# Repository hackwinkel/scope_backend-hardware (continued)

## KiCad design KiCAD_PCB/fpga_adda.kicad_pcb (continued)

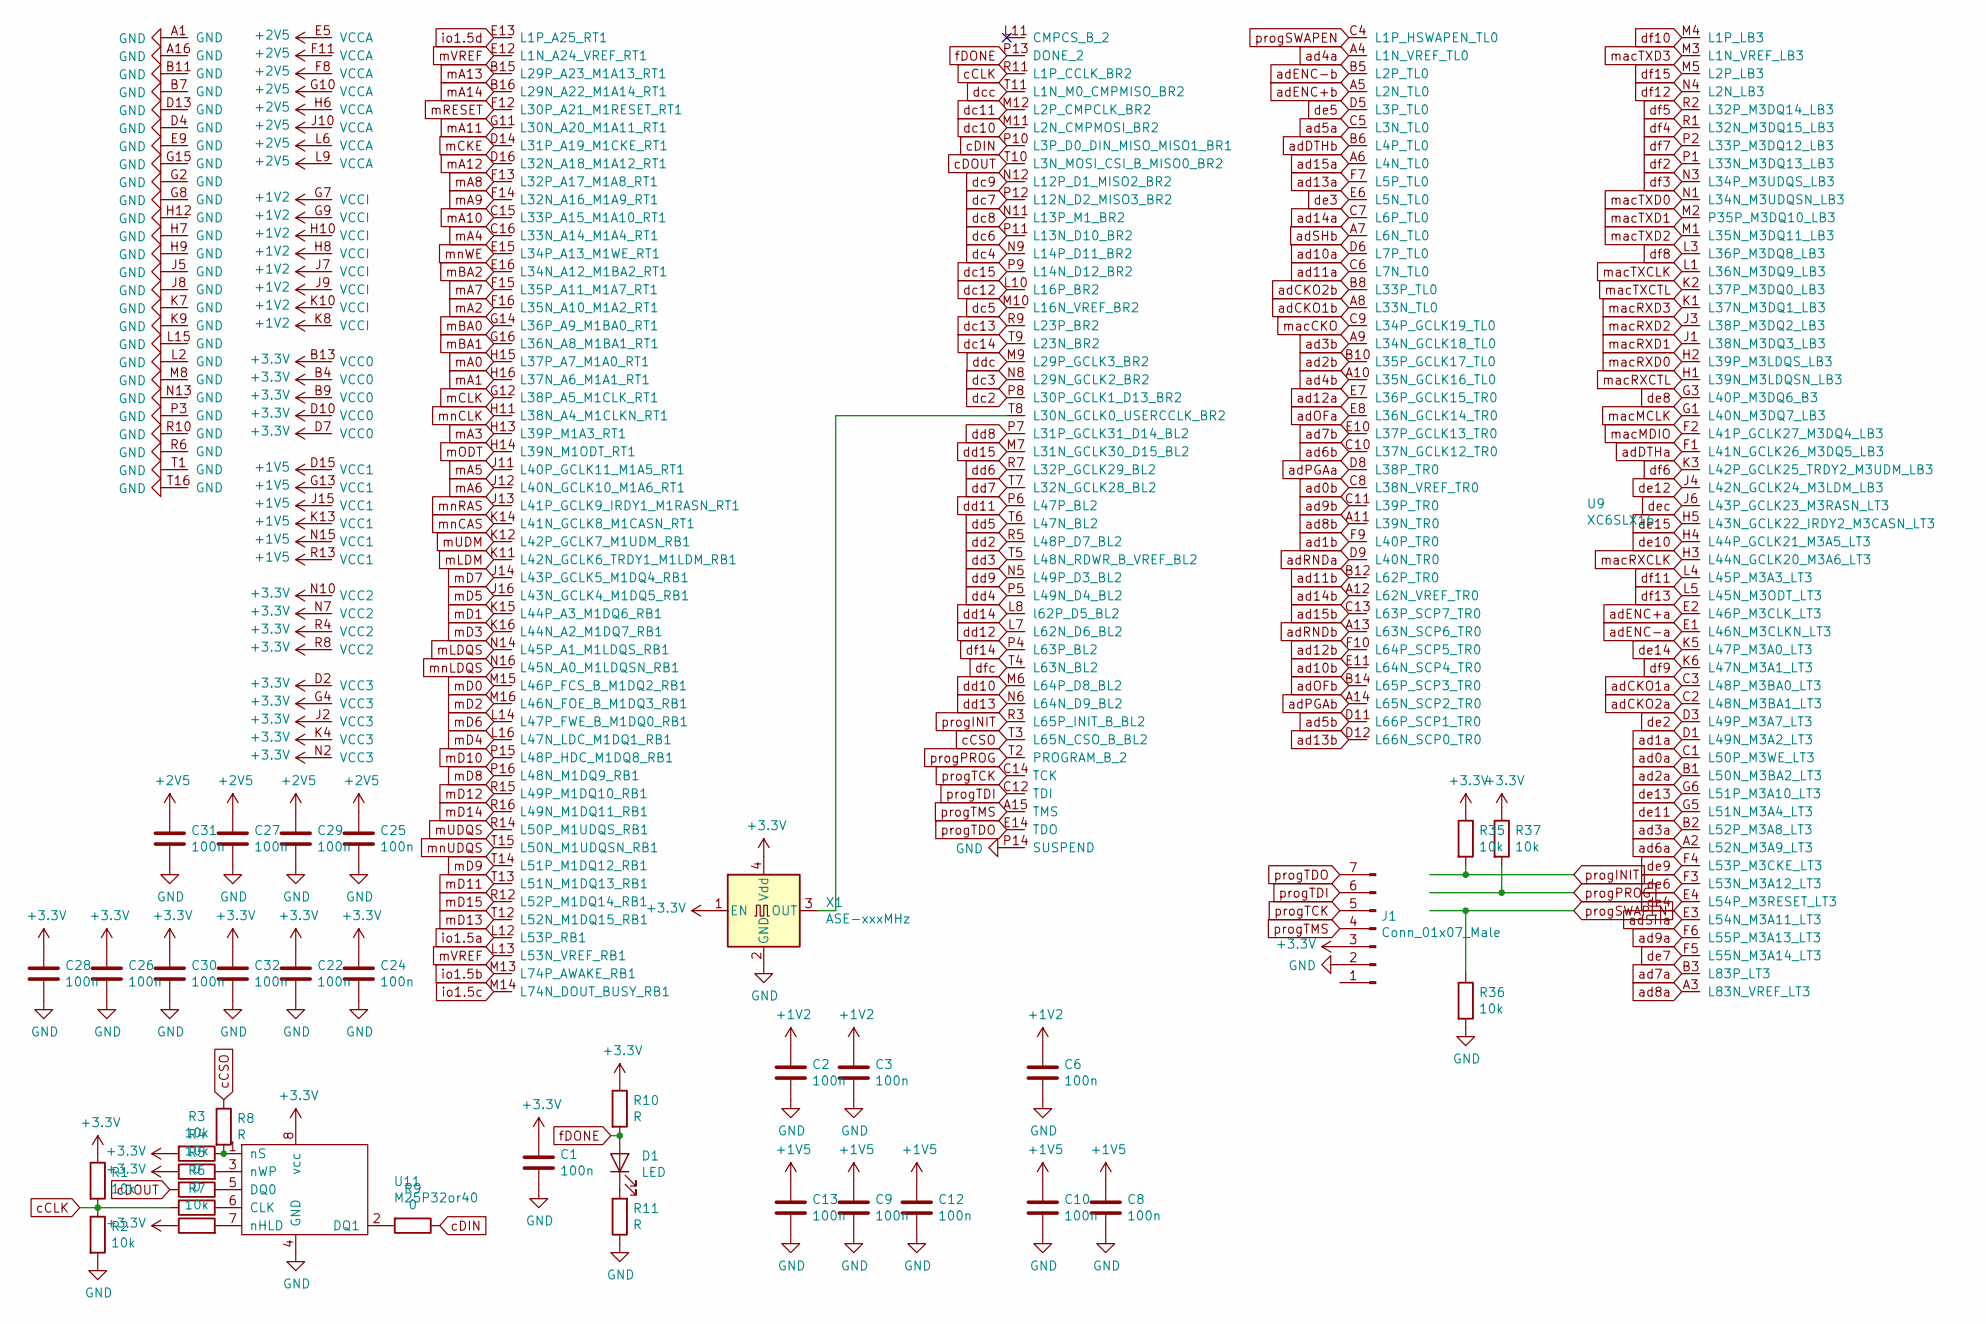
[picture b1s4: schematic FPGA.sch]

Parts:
C1, C2, C3, C6, C8, C9, C10, C12, C13, C22, C24, C25, C26, C27, C28, C29, C30, C31, C32: 100n; C_0805_2012Metric_Pad1.15x1.40mm_HandSolder
D1: LED; LED_0805_2012Metric_Pad1.15x1.40mm_HandSolder
J1: Conn_01x07_Male; jtagconn
R1, R2, R3, R4, R7, R35, R36, R37: 10k; R_0805_2012Metric_Pad1.15x1.40mm_HandSolder
R5, R6, R9: 0; R_0805_2012Metric_Pad1.15x1.40mm_HandSolder
R8, R10, R11: R; R_0805_2012Metric_Pad1.15x1.40mm_HandSolder
U9: XC6SLX16; xc6_FTG256
U11: M25P32or40
X1: ASE-xxxMHz; Oscillator_SMD_Abracon_ASV-4Pin_7.0x5.1mm_HandSoldering

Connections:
+1V2: C2.1, C3.1, C6.1, U9.G7 (VCCI), U9.G9 (VCCI), U9.H8 (VCCI), U9.H10 (VCCI), U9.J7 (VCCI), U9.J9 (VCCI), U9.K8 (VCCI), U9.K10 (VCCI); also elsewhere on the board
+1V5: C8.1, C9.1, C10.1, C12.1, C13.1, U9.D15 (VCC1), U9.G13 (VCC1), U9.J15 (VCC1), U9.K13 (VCC1), U9.N15 (VCC1), U9.R13 (VCC1); also elsewhere on the board
+2V5: C25.1, C27.1, C29.1, C31.1, U9.E5 (VCCA), U9.F8 (VCCA), U9.F11 (VCCA), U9.G10 (VCCA), U9.H6 (VCCA), U9.J10 (VCCA), U9.L6 (VCCA), U9.L9 (VCCA); also elsewhere on the board
GND: C1.2, C2.2, C3.2, C6.2, C8.2, C9.2, C10.2, C12.2, C13.2, C22.2, C24.2, C25.2, C26.2, C27.2, C28.2, C29.2, C30.2, C31.2, C32.2, J1.2, R2.2, R11.1, R36.2, U9.A1 (GND), U9.A16 (GND), U9.B7 (GND), U9.B11 (GND), U9.D4 (GND), U9.D13 (GND), U9.E9 (GND), U9.G2 (GND), U9.G8 (GND), U9.G15 (GND), U9.H7 (GND), U9.H9 (GND), U9.H12 (GND), U9.J5 (GND), U9.J8 (GND), U9.K7 (GND), U9.K9 (GND), U9.L2 (GND), U9.L15 (GND), U9.M8 (GND), U9.N13 (GND), U9.P3 (GND), U9.P14 (SUSPEND), U9.R6 (GND), U9.R10 (GND), U9.T1 (GND), U9.T16 (GND), U11.4 (GND), X1.2 (GND); also elsewhere on the board
unnamed: D1.1 (K), R11.2
unnamed: R3.1, R8.2, U11.1 (nS)
unnamed: R4.2, U11.3 (nWP)
unnamed: R5.1, U11.5 (DQ0)
unnamed: R6.1, U11.6 (CLK)
unnamed: R7.2, U11.7 (nHLD)
unnamed: R9.2, U11.2 (DQ1)
unnamed: U9.T8 (L30N_GCLK0_USERCCLK_BR2), X1.3 (OUT)
ad0a: U9.C1 (L50P_M3WE_LT3); also elsewhere on the board
ad0b: U9.C8 (L38N_VREF_TR0); also elsewhere on the board
ad1a: U9.D1 (L49N_M3A2_LT3); also elsewhere on the board
ad1b: U9.F9 (L40P_TR0); also elsewhere on the board
ad2a: U9.B1 (L50N_M3BA2_LT3); also elsewhere on the board
ad2b: U9.B10 (L35P_GCLK17_TL0); also elsewhere on the board
ad3a: U9.B2 (L52P_M3A8_LT3); also elsewhere on the board
ad3b: U9.A9 (L34N_GCLK18_TL0); also elsewhere on the board
ad4a: U9.A4 (L1N_VREF_TL0); also elsewhere on the board
ad4b: U9.A10 (L35N_GCLK16_TL0); also elsewhere on the board
ad5a: U9.C5 (L3N_TL0); also elsewhere on the board
ad5b: U9.D11 (L66P_SCP1_TR0); also elsewhere on the board
ad6a: U9.A2 (L52N_M3A9_LT3); also elsewhere on the board
ad6b: U9.C10 (L37N_GCLK12_TR0); also elsewhere on the board
ad7a: U9.B3 (L83P_LT3); also elsewhere on the board
ad7b: U9.E10 (L37P_GCLK13_TR0); also elsewhere on the board
ad8a: U9.A3 (L83N_VREF_LT3); also elsewhere on the board
ad8b: U9.A11 (L39N_TR0); also elsewhere on the board
ad9a: U9.F6 (L55P_M3A13_LT3); also elsewhere on the board
ad9b: U9.C11 (L39P_TR0); also elsewhere on the board
ad10a: U9.D6 (L7P_TL0); also elsewhere on the board
ad10b: U9.E11 (L64N_SCP4_TR0); also elsewhere on the board
ad11a: U9.C6 (L7N_TL0); also elsewhere on the board
ad11b: U9.B12 (L62P_TR0); also elsewhere on the board
ad12a: U9.E7 (L36P_GCLK15_TR0); also elsewhere on the board
ad12b: U9.F10 (L64P_SCP5_TR0); also elsewhere on the board
ad13a: U9.F7 (L5P_TL0); also elsewhere on the board
ad13b: U9.D12 (L66N_SCP0_TR0); also elsewhere on the board
ad14a: U9.C7 (L6P_TL0); also elsewhere on the board
ad14b: U9.A12 (L62N_VREF_TR0); also elsewhere on the board
ad15a: U9.A6 (L4N_TL0); also elsewhere on the board
ad15b: U9.C13 (L63P_SCP7_TR0); also elsewhere on the board
adCKO1a: U9.C3 (L48P_M3BA0_LT3); also elsewhere on the board
adCKO1b: U9.A8 (L33N_TL0); also elsewhere on the board
adCKO2a: U9.C2 (L48N_M3BA1_LT3); also elsewhere on the board
adCKO2b: U9.B8 (L33P_TL0); also elsewhere on the board
adDTHa: U9.F1 (L41N_GCLK26_M3DQ5_LB3); also elsewhere on the board
adDTHb: U9.B6 (L4P_TL0); also elsewhere on the board
adENC+a: U9.E2 (L46P_M3CLK_LT3); also elsewhere on the board
adENC+b: U9.A5 (L2N_TL0); also elsewhere on the board
adENC-a: U9.E1 (L46N_M3CLKN_LT3); also elsewhere on the board
adENC-b: U9.B5 (L2P_TL0); also elsewhere on the board
adOFa: U9.E8 (L36N_GCLK14_TR0); also elsewhere on the board
adOFb: U9.B14 (L65P_SCP3_TR0); also elsewhere on the board
adPGAa: U9.D8 (L38P_TR0); also elsewhere on the board
adPGAb: U9.A14 (L65N_SCP2_TR0); also elsewhere on the board
adRNDa: U9.D9 (L40N_TR0); also elsewhere on the board
adRNDb: U9.A13 (L63N_SCP6_TR0); also elsewhere on the board
adSHa: U9.E3 (L54N_M3A11_LT3); also elsewhere on the board
adSHb: U9.A7 (L6N_TL0); also elsewhere on the board
cCLK: R1.2, R2.1, R6.2, U9.R11 (L1P_CCLK_BR2)
cCSO: R8.1, U9.T3 (L65N_CSO_B_BL2)
cDIN: R9.1, U9.P10 (L3P_D0_DIN_MISO_MISO1_BR1)
cDOUT: R5.2, U9.T10 (L3N_MOSI_CSI_B_MISO0_BR2)
dc2: U9.P8 (L30P_GCLK1_D13_BR2); also elsewhere on the board
dc3: U9.N8 (L29N_GCLK2_BR2); also elsewhere on the board
dc4: U9.N9 (L14P_D11_BR2); also elsewhere on the board
dc5: U9.M10 (L16N_VREF_BR2); also elsewhere on the board
dc6: U9.P11 (L13N_D10_BR2); also elsewhere on the board
dc7: U9.P12 (L12N_D2_MISO3_BR2); also elsewhere on the board
dc8: U9.N11 (L13P_M1_BR2); also elsewhere on the board
dc9: U9.N12 (L12P_D1_MISO2_BR2); also elsewhere on the board
dc10: U9.M11 (L2N_CMPMOSI_BR2); also elsewhere on the board
dc11: U9.M12 (L2P_CMPCLK_BR2); also elsewhere on the board
dc12: U9.L10 (L16P_BR2); also elsewhere on the board
dc13: U9.R9 (L23P_BR2); also elsewhere on the board
dc14: U9.T9 (L23N_BR2); also elsewhere on the board
dc15: U9.P9 (L14N_D12_BR2); also elsewhere on the board
dcc: U9.T11 (L1N_M0_CMPMISO_BR2); also elsewhere on the board
dd2: U9.R5 (L48P_D7_BL2); also elsewhere on the board
dd3: U9.T5 (L48N_RDWR_B_VREF_BL2); also elsewhere on the board
dd4: U9.P5 (L49N_D4_BL2); also elsewhere on the board
dd5: U9.T6 (L47N_BL2); also elsewhere on the board
dd6: U9.R7 (L32P_GCLK29_BL2); also elsewhere on the board
dd7: U9.T7 (L32N_GCLK28_BL2); also elsewhere on the board
dd8: U9.P7 (L31P_GCLK31_D14_BL2); also elsewhere on the board
dd9: U9.N5 (L49P_D3_BL2); also elsewhere on the board
dd10: U9.M6 (L64P_D8_BL2); also elsewhere on the board
dd11: U9.P6 (L47P_BL2); also elsewhere on the board
dd12: U9.L7 (L62N_D6_BL2); also elsewhere on the board
dd13: U9.N6 (L64N_D9_BL2); also elsewhere on the board
dd14: U9.L8 (l62P_D5_BL2); also elsewhere on the board
dd15: U9.M7 (L31N_GCLK30_D15_BL2); also elsewhere on the board
ddc: U9.M9 (L29P_GCLK3_BR2); also elsewhere on the board
de2: U9.D3 (L49P_M3A7_LT3); also elsewhere on the board
de3: U9.E6 (L5N_TL0); also elsewhere on the board
de4: U9.E4 (L54P_M3RESET_LT3); also elsewhere on the board
de5: U9.D5 (L3P_TL0); also elsewhere on the board
de6: U9.F3 (L53N_M3A12_LT3); also elsewhere on the board
de7: U9.F5 (L55N_M3A14_LT3); also elsewhere on the board
de8: U9.G3 (L40P_M3DQ6_B3); also elsewhere on the board
de9: U9.F4 (L53P_M3CKE_LT3); also elsewhere on the board
de10: U9.H4 (L44P_GCLK21_M3A5_LT3); also elsewhere on the board
de11: U9.G5 (L51N_M3A4_LT3); also elsewhere on the board
de12: U9.J4 (L42N_GCLK24_M3LDM_LB3); also elsewhere on the board
de13: U9.G6 (L51P_M3A10_LT3); also elsewhere on the board
de14: U9.K5 (L47P_M3A0_LT3); also elsewhere on the board
de15: U9.H5 (L43N_GCLK22_IRDY2_M3CASN_LT3); also elsewhere on the board
dec: U9.J6 (L43P_GCLK23_M3RASN_LT3); also elsewhere on the board
df2: U9.P1 (L33N_M3DQ13_LB3); also elsewhere on the board
df3: U9.N3 (L34P_M3UDQS_LB3); also elsewhere on the board
df4: U9.R1 (L32N_M3DQ15_LB3); also elsewhere on the board
df5: U9.R2 (L32P_M3DQ14_LB3); also elsewhere on the board
df6: U9.K3 (L42P_GCLK25_TRDY2_M3UDM_LB3); also elsewhere on the board
df7: U9.P2 (L33P_M3DQ12_LB3); also elsewhere on the board
df8: U9.L3 (L36P_M3DQ8_LB3); also elsewhere on the board
df9: U9.K6 (L47N_M3A1_LT3); also elsewhere on the board
df10: U9.M4 (L1P_LB3); also elsewhere on the board
df11: U9.L4 (L45P_M3A3_LT3); also elsewhere on the board
df12: U9.N4 (L2N_LB3); also elsewhere on the board
df13: U9.L5 (L45N_M3ODT_LT3); also elsewhere on the board
df14: U9.P4 (L63P_BL2); also elsewhere on the board
df15: U9.M5 (L2P_LB3); also elsewhere on the board
dfc: U9.T4 (L63N_BL2); also elsewhere on the board
fDONE: D1.2 (A), R10.2, U9.P13 (DONE_2)
io1.5a: U9.L12 (L53P_RB1)
io1.5b: U9.M13 (L74P_AWAKE_RB1)
io1.5c: U9.M14 (L74N_DOUT_BUSY_RB1)
io1.5d: U9.E13 (L1P_A25_RT1)
mA0: U9.H15 (L37P_A7_M1A0_RT1); also elsewhere on the board
mA1: U9.H16 (L37N_A6_M1A1_RT1); also elsewhere on the board
mA2: U9.F16 (L35N_A10_M1A2_RT1); also elsewhere on the board
mA3: U9.H13 (L39P_M1A3_RT1); also elsewhere on the board
mA4: U9.C16 (L33N_A14_M1A4_RT1); also elsewhere on the board
mA5: U9.J11 (L40P_GCLK11_M1A5_RT1); also elsewhere on the board
mA6: U9.J12 (L40N_GCLK10_M1A6_RT1); also elsewhere on the board
mA7: U9.F15 (L35P_A11_M1A7_RT1); also elsewhere on the board
mA8: U9.F13 (L32P_A17_M1A8_RT1); also elsewhere on the board
mA9: U9.F14 (L32N_A16_M1A9_RT1); also elsewhere on the board
mA10: U9.C15 (L33P_A15_M1A10_RT1); also elsewhere on the board
mA11: U9.G11 (L30N_A20_M1A11_RT1); also elsewhere on the board
mA12: U9.D16 (L32N_A18_M1A12_RT1); also elsewhere on the board
mA13: U9.B15 (L29P_A23_M1A13_RT1); also elsewhere on the board
mA14: U9.B16 (L29N_A22_M1A14_RT1); also elsewhere on the board
mBA0: U9.G14 (L36P_A9_M1BA0_RT1); also elsewhere on the board
mBA1: U9.G16 (L36N_A8_M1BA1_RT1); also elsewhere on the board
mBA2: U9.E16 (L34N_A12_M1BA2_RT1); also elsewhere on the board
mCKE: U9.D14 (L31P_A19_M1CKE_RT1); also elsewhere on the board
mCLK: U9.G12 (L38P_A5_M1CLK_RT1); also elsewhere on the board
mD0: U9.M15 (L46P_FCS_B_M1DQ2_RB1); also elsewhere on the board
mD1: U9.K15 (L44P_A3_M1DQ6_RB1); also elsewhere on the board
mD2: U9.M16 (L46N_FOE_B_M1DQ3_RB1); also elsewhere on the board
mD3: U9.K16 (L44N_A2_M1DQ7_RB1); also elsewhere on the board
mD4: U9.L16 (L47N_LDC_M1DQ1_RB1); also elsewhere on the board
mD5: U9.J16 (L43N_GCLK4_M1DQ5_RB1); also elsewhere on the board
mD6: U9.L14 (L47P_FWE_B_M1DQ0_RB1); also elsewhere on the board
mD7: U9.J14 (L43P_GCLK5_M1DQ4_RB1); also elsewhere on the board
mD8: U9.P16 (L48N_M1DQ9_RB1); also elsewhere on the board
mD9: U9.T14 (L51P_M1DQ12_RB1); also elsewhere on the board
mD10: U9.P15 (L48P_HDC_M1DQ8_RB1); also elsewhere on the board
mD11: U9.T13 (L51N_M1DQ13_RB1); also elsewhere on the board
mD12: U9.R15 (L49P_M1DQ10_RB1); also elsewhere on the board
mD13: U9.T12 (L52N_M1DQ15_RB1); also elsewhere on the board
mD14: U9.R16 (L49N_M1DQ11_RB1); also elsewhere on the board
mD15: U9.R12 (L52P_M1DQ14_RB1); also elsewhere on the board
mLDM: U9.K11 (L42N_GCLK6_TRDY1_M1LDM_RB1); also elsewhere on the board
mLDQS: U9.N14 (L45P_A1_M1LDQS_RB1); also elsewhere on the board
mODT: U9.H14 (L39N_M1ODT_RT1); also elsewhere on the board
mRESET: U9.F12 (L30P_A21_M1RESET_RT1); also elsewhere on the board
mUDM: U9.K12 (L42P_GCLK7_M1UDM_RB1); also elsewhere on the board
mUDQS: U9.R14 (L50P_M1UDQS_RB1); also elsewhere on the board
mVREF: U9.E12 (L1N_A24_VREF_RT1), U9.L13 (L53N_VREF_RB1); also elsewhere on the board
macCKO: U9.C9 (L34P_GCLK19_TL0); also elsewhere on the board
macMCLK: U9.G1 (L40N_M3DQ7_LB3); also elsewhere on the board
macMDIO: U9.F2 (L41P_GCLK27_M3DQ4_LB3); also elsewhere on the board
macRXCLK: U9.H3 (L44N_GCLK20_M3A6_LT3); also elsewhere on the board
macRXCTL: U9.H1 (L39N_M3LDQSN_LB3); also elsewhere on the board
macRXD0: U9.H2 (L39P_M3LDQS_LB3); also elsewhere on the board
macRXD1: U9.J1 (L38N_M3DQ3_LB3); also elsewhere on the board
macRXD2: U9.J3 (L38P_M3DQ2_LB3); also elsewhere on the board
macRXD3: U9.K1 (L37N_M3DQ1_LB3); also elsewhere on the board
macTXCLK: U9.L1 (L36N_M3DQ9_LB3); also elsewhere on the board
macTXCTL: U9.K2 (L37P_M3DQ0_LB3); also elsewhere on the board
macTXD0: U9.N1 (L34N_M3UDQSN_LB3); also elsewhere on the board
macTXD1: U9.M2 (P35P_M3DQ10_LB3); also elsewhere on the board
macTXD2: U9.M1 (L35N_M3DQ11_LB3); also elsewhere on the board
macTXD3: U9.M3 (L1N_VREF_LB3); also elsewhere on the board
mnCAS: U9.K14 (L41N_GCLK8_M1CASN_RT1); also elsewhere on the board
mnCLK: U9.H11 (L38N_A4_M1CLKN_RT1); also elsewhere on the board
mnLDQS: U9.N16 (L45N_A0_M1LDQSN_RB1); also elsewhere on the board
mnRAS: U9.J13 (L41P_GCLK9_IRDY1_M1RASN_RT1); also elsewhere on the board
mnUDQS: U9.T15 (L50N_M1UDQSN_RB1); also elsewhere on the board
mnWE: U9.E15 (L34P_A13_M1WE_RT1); also elsewhere on the board
progINIT: R35.2, U9.R3 (L65P_INIT_B_BL2)
progPROG: R37.2, U9.T2 (PROGRAM_B_2)
progSWAPEN: R36.1, U9.C4 (L1P_HSWAPEN_TL0)
progTCK: J1.5, U9.C14 (TCK)
progTDI: J1.6, U9.C12 (TDI)
progTDO: J1.7, U9.E14 (TDO)
progTMS: J1.4, U9.A15 (TMS)

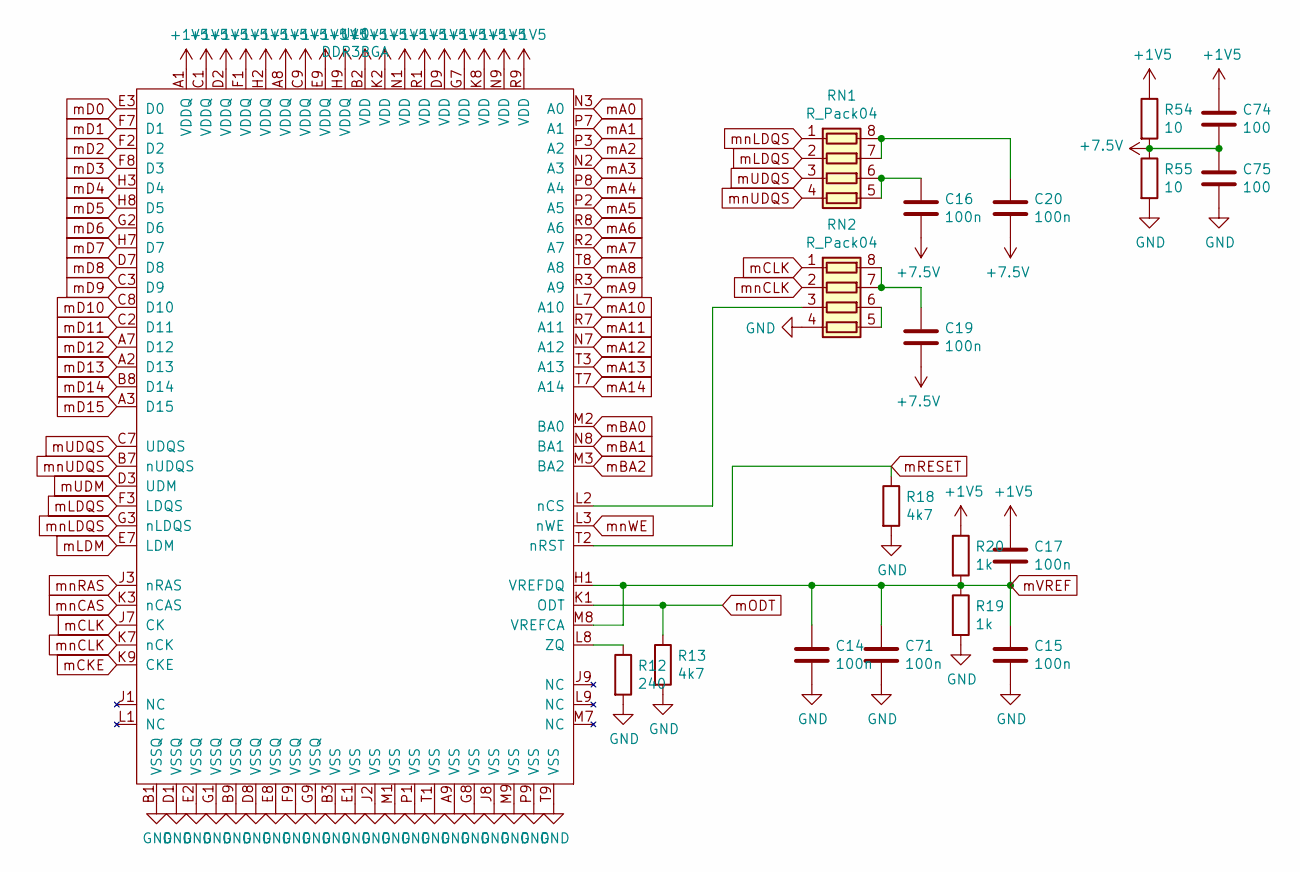
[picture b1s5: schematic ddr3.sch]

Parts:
C14, C15, C16, C17, C19, C20, C71: 100n; C_0805_2012Metric_Pad1.15x1.40mm_HandSolder
C74, C75: 100; C_0805_2012Metric_Pad1.15x1.40mm_HandSolder
R12: 240; R_0805_2012Metric_Pad1.15x1.40mm_HandSolder
R13, R18: 4k7; R_0805_2012Metric_Pad1.15x1.40mm_HandSolder
R19, R20: 1k; R_0805_2012Metric_Pad1.15x1.40mm_HandSolder
R54, R55: 10; R_0805_2012Metric_Pad1.15x1.40mm_HandSolder
RN1, RN2: R_Pack04; R_Array_Concave_4x0603
U10: DDR3BGA; ddr3bga

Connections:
+1V5: C17.1, C74.1, R20.1, R54.1, U10.A1 (VDDQ), U10.A8 (VDDQ), U10.B2 (VDD), U10.C1 (VDDQ), U10.C9 (VDDQ), U10.D2 (VDDQ), U10.D9 (VDD), U10.E9 (VDDQ), U10.F1 (VDDQ), U10.G7 (VDD), U10.H2 (VDDQ), U10.H9 (VDDQ), U10.K2 (VDD), U10.K8 (VDD), U10.N1 (VDD), U10.N9 (VDD), U10.R1 (VDD), U10.R9 (VDD); also elsewhere on the board
+7.5V: C16.2, C19.2, C20.2, C74.2, C75.1, R54.2, R55.1
GND: C14.2, C15.2, C71.2, C75.2, R12.2, R13.2, R18.2, R19.2, R55.2, RN2.4 (R4.1), U10.A9 (VSS), U10.B1 (VSSQ), U10.B3 (VSS), U10.B9 (VSSQ), U10.D1 (VSSQ), U10.D8 (VSSQ), U10.E1 (VSS), U10.E2 (VSSQ), U10.E8 (VSSQ), U10.F9 (VSSQ), U10.G1 (VSSQ), U10.G8 (VSS), U10.G9 (VSSQ), U10.J2 (VSS), U10.J8 (VSS), U10.M1 (VSS), U10.M9 (VSS), U10.P1 (VSS), U10.P9 (VSS), U10.T1 (VSS), U10.T9 (VSS); also elsewhere on the board
unnamed: C16.1, RN1.5 (R4.2), RN1.6 (R3.2)
unnamed: C19.1, RN2.7 (R2.2), RN2.8 (R1.2)
unnamed: C20.1, RN1.7 (R2.2), RN1.8 (R1.2)
unnamed: R12.1, U10.L8 (ZQ)
unnamed: RN2.3 (R3.1), U10.L2 (nCS)
unnamed: RN2.5 (R4.2), RN2.6 (R3.2)
mA0: U10.N3 (A0); also elsewhere on the board
mA1: U10.P7 (A1); also elsewhere on the board
mA2: U10.P3 (A2); also elsewhere on the board
mA3: U10.N2 (A3); also elsewhere on the board
mA4: U10.P8 (A4); also elsewhere on the board
mA5: U10.P2 (A5); also elsewhere on the board
mA6: U10.R8 (A6); also elsewhere on the board
mA7: U10.R2 (A7); also elsewhere on the board
mA8: U10.T8 (A8); also elsewhere on the board
mA9: U10.R3 (A9); also elsewhere on the board
mA10: U10.L7 (A10); also elsewhere on the board
mA11: U10.R7 (A11); also elsewhere on the board
mA12: U10.N7 (A12); also elsewhere on the board
mA13: U10.T3 (A13); also elsewhere on the board
mA14: U10.T7 (A14); also elsewhere on the board
mBA0: U10.M2 (BA0); also elsewhere on the board
mBA1: U10.N8 (BA1); also elsewhere on the board
mBA2: U10.M3 (BA2); also elsewhere on the board
mCKE: U10.K9 (CKE); also elsewhere on the board
mCLK: RN2.1 (R1.1), U10.J7 (CK); also elsewhere on the board
mD0: U10.E3 (D0); also elsewhere on the board
mD1: U10.F7 (D1); also elsewhere on the board
mD2: U10.F2 (D2); also elsewhere on the board
mD3: U10.F8 (D3); also elsewhere on the board
mD4: U10.H3 (D4); also elsewhere on the board
mD5: U10.H8 (D5); also elsewhere on the board
mD6: U10.G2 (D6); also elsewhere on the board
mD7: U10.H7 (D7); also elsewhere on the board
mD8: U10.D7 (D8); also elsewhere on the board
mD9: U10.C3 (D9); also elsewhere on the board
mD10: U10.C8 (D10); also elsewhere on the board
mD11: U10.C2 (D11); also elsewhere on the board
mD12: U10.A7 (D12); also elsewhere on the board
mD13: U10.A2 (D13); also elsewhere on the board
mD14: U10.B8 (D14); also elsewhere on the board
mD15: U10.A3 (D15); also elsewhere on the board
mLDM: U10.E7 (LDM); also elsewhere on the board
mLDQS: RN1.2 (R2.1), U10.F3 (LDQS); also elsewhere on the board
mODT: R13.1, U10.K1 (ODT); also elsewhere on the board
mRESET: R18.1, U10.T2 (nRST); also elsewhere on the board
mUDM: U10.D3 (UDM); also elsewhere on the board
mUDQS: RN1.3 (R3.1), U10.C7 (UDQS); also elsewhere on the board
mVREF: C14.1, C15.1, C17.2, C71.1, R19.1, R20.2, U10.H1 (VREFDQ), U10.M8 (VREFCA); also elsewhere on the board
mnCAS: U10.K3 (nCAS); also elsewhere on the board
mnCLK: RN2.2 (R2.1), U10.K7 (nCK); also elsewhere on the board
mnLDQS: RN1.1 (R1.1), U10.G3 (nLDQS); also elsewhere on the board
mnRAS: U10.J3 (nRAS); also elsewhere on the board
mnUDQS: RN1.4 (R4.1), U10.B7 (nUDQS); also elsewhere on the board
mnWE: U10.L3 (nWE); also elsewhere on the board

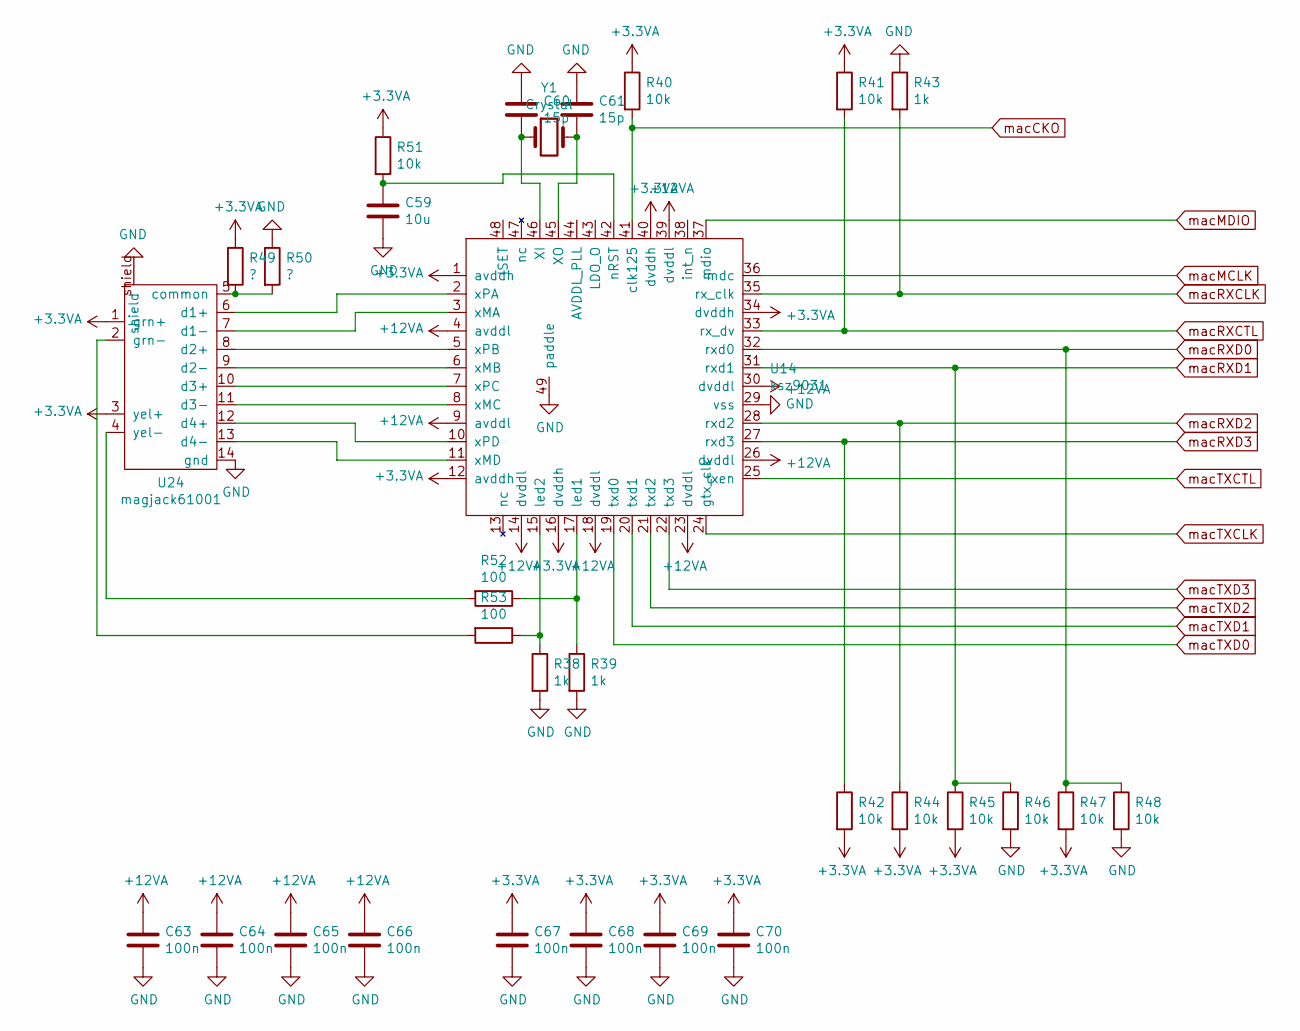
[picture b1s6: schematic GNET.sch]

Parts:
C59: 10u; C_0805_2012Metric_Pad1.15x1.40mm_HandSolder
C60, C61: 15p; C_0805_2012Metric_Pad1.15x1.40mm_HandSolder
C63, C64, C65, C66, C67, C68, C69, C70: 100n; C_0805_2012Metric_Pad1.15x1.40mm_HandSolder
R38, R39, R43: 1k; R_0805_2012Metric_Pad1.15x1.40mm_HandSolder
R40, R41, R42, R44, R45, R46, R47, R48, R51: 10k; R_0805_2012Metric_Pad1.15x1.40mm_HandSolder
R49, R50: ?; R_0805_2012Metric_Pad1.15x1.40mm_HandSolder
R52, R53: 100; R_0805_2012Metric_Pad1.15x1.40mm_HandSolder
U14: ksz9031; qfn49_0.5_7x7
U24: magjack61001
Y1: Crystal; xtal

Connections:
+3.3VA: C67.1, C68.1, C69.1, C70.1, R40.1, R41.1, R42.2, R44.2, R45.2, R47.2, R49.1, R51.1, U14.1 (avddh), U14.12 (avddh), U14.16 (dvddh), U14.34 (dvddh), U14.40 (dvddh), U24.1 (grn+), U24.3 (yel+); also elsewhere on the board
+12VA: C63.1, C64.1, C65.1, C66.1, U14.4 (avddl), U14.9 (avddl), U14.14 (dvddl), U14.18 (dvddl), U14.23 (dvddl), U14.26 (dvddl), U14.30 (dvddl), U14.39 (dvddl); also elsewhere on the board
GND: C59.2, C60.1, C61.1, C63.2, C64.2, C65.2, C66.2, C67.2, C68.2, C69.2, C70.2, R38.2, R39.2, R43.1, R46.2, R48.2, R50.1, U14.29 (vss), U14.49 (paddle), U24.14 (gnd), U24.shield; also elsewhere on the board
unnamed: C59.1, R51.2, U14.42 (nRST)
unnamed: C60.2, U14.46 (XI), Y1.1
unnamed: C61.2, U14.45 (XO), Y1.2
unnamed: R38.1, R53.1, U14.15 (led2)
unnamed: R39.1, R52.1, U14.17 (led1)
unnamed: R49.2, R50.2, U24.5 (common)
unnamed: R52.2, U24.4 (yel-)
unnamed: R53.2, U24.2 (grn-)
unnamed: U14.2 (xPA), U24.6 (d1+)
unnamed: U14.3 (xMA), U24.7 (d1-)
unnamed: U14.5 (xPB), U24.8 (d2+)
unnamed: U14.6 (xMB), U24.9 (d2-)
unnamed: U14.7 (xPC), U24.10 (d3+)
unnamed: U14.8 (xMC), U24.11 (d3-)
unnamed: U14.10 (xPD), U24.12 (d4+)
unnamed: U14.11 (xMD), U24.13 (d4-)
macCKO: R40.2, U14.41 (clk125); also elsewhere on the board
macMCLK: U14.36 (mdc); also elsewhere on the board
macMDIO: U14.37 (mdio); also elsewhere on the board
macRXCLK: R43.2, U14.35 (rx_clk); also elsewhere on the board
macRXCTL: R41.2, U14.33 (rx_dv); also elsewhere on the board
macRXD0: R47.1, R48.1, U14.32 (rxd0); also elsewhere on the board
macRXD1: R45.1, R46.1, U14.31 (rxd1); also elsewhere on the board
macRXD2: R44.1, U14.28 (rxd2); also elsewhere on the board
macRXD3: R42.1, U14.27 (rxd3); also elsewhere on the board
macTXCLK: U14.24 (gtx_clk); also elsewhere on the board
macTXCTL: U14.25 (txen); also elsewhere on the board
macTXD0: U14.19 (txd0); also elsewhere on the board
macTXD1: U14.20 (txd1); also elsewhere on the board
macTXD2: U14.21 (txd2); also elsewhere on the board
macTXD3: U14.22 (txd3); also elsewhere on the board

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
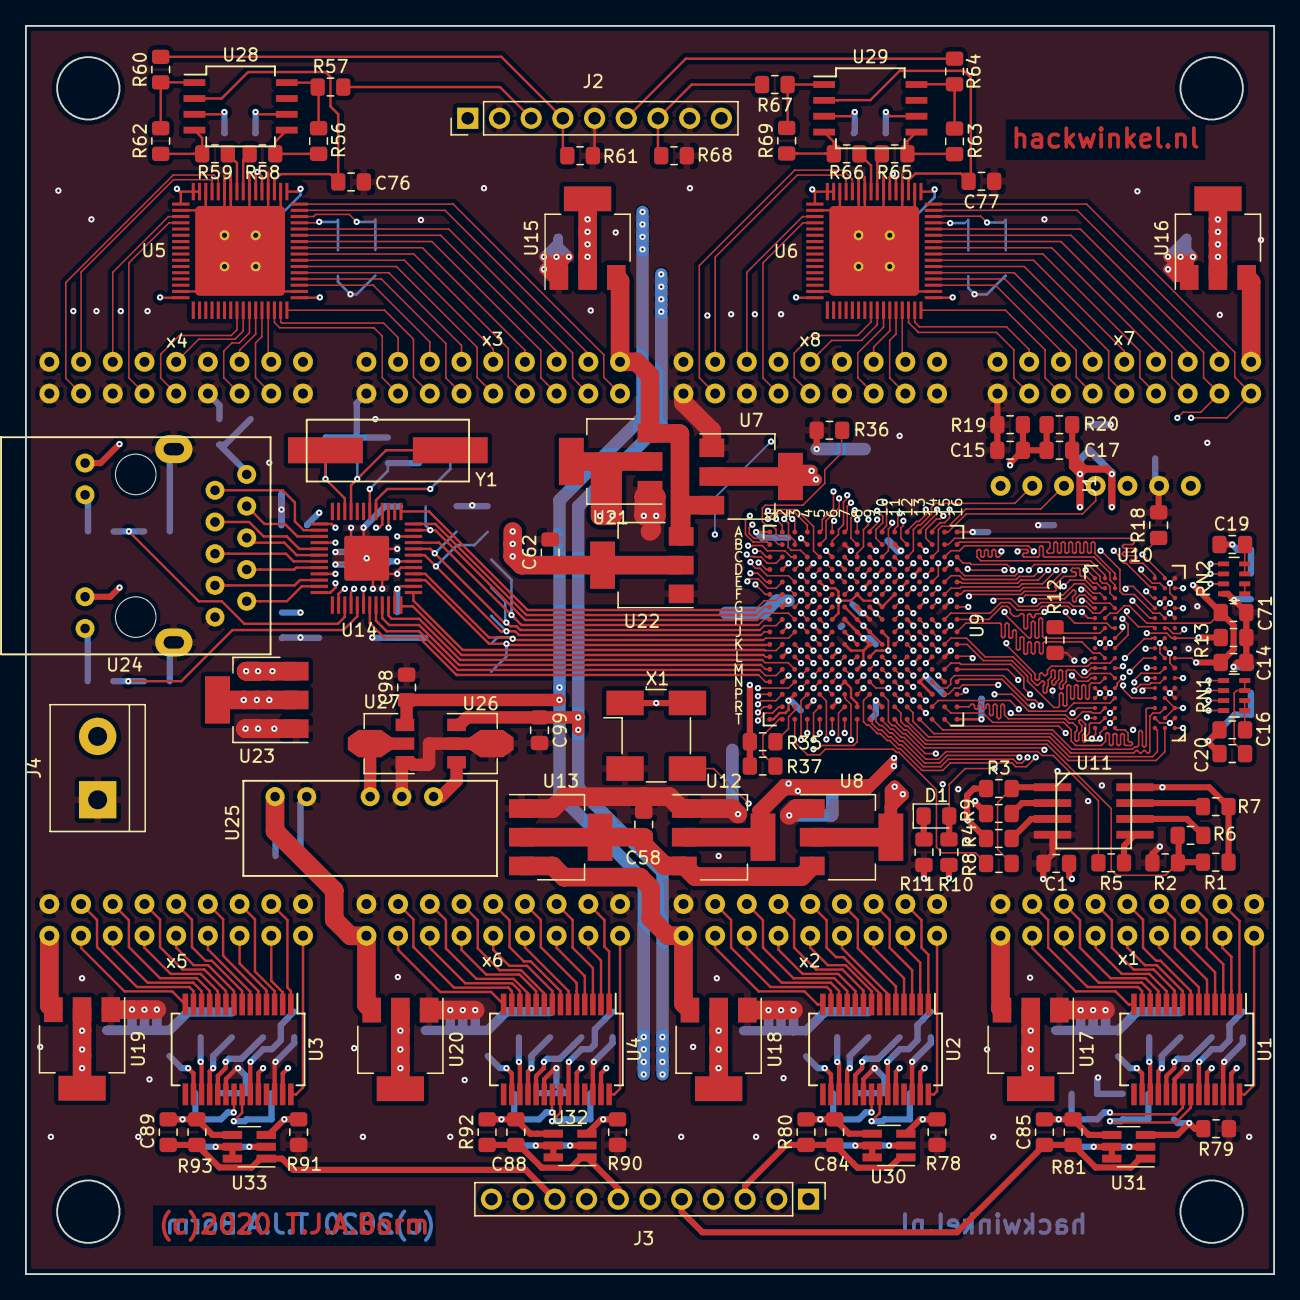
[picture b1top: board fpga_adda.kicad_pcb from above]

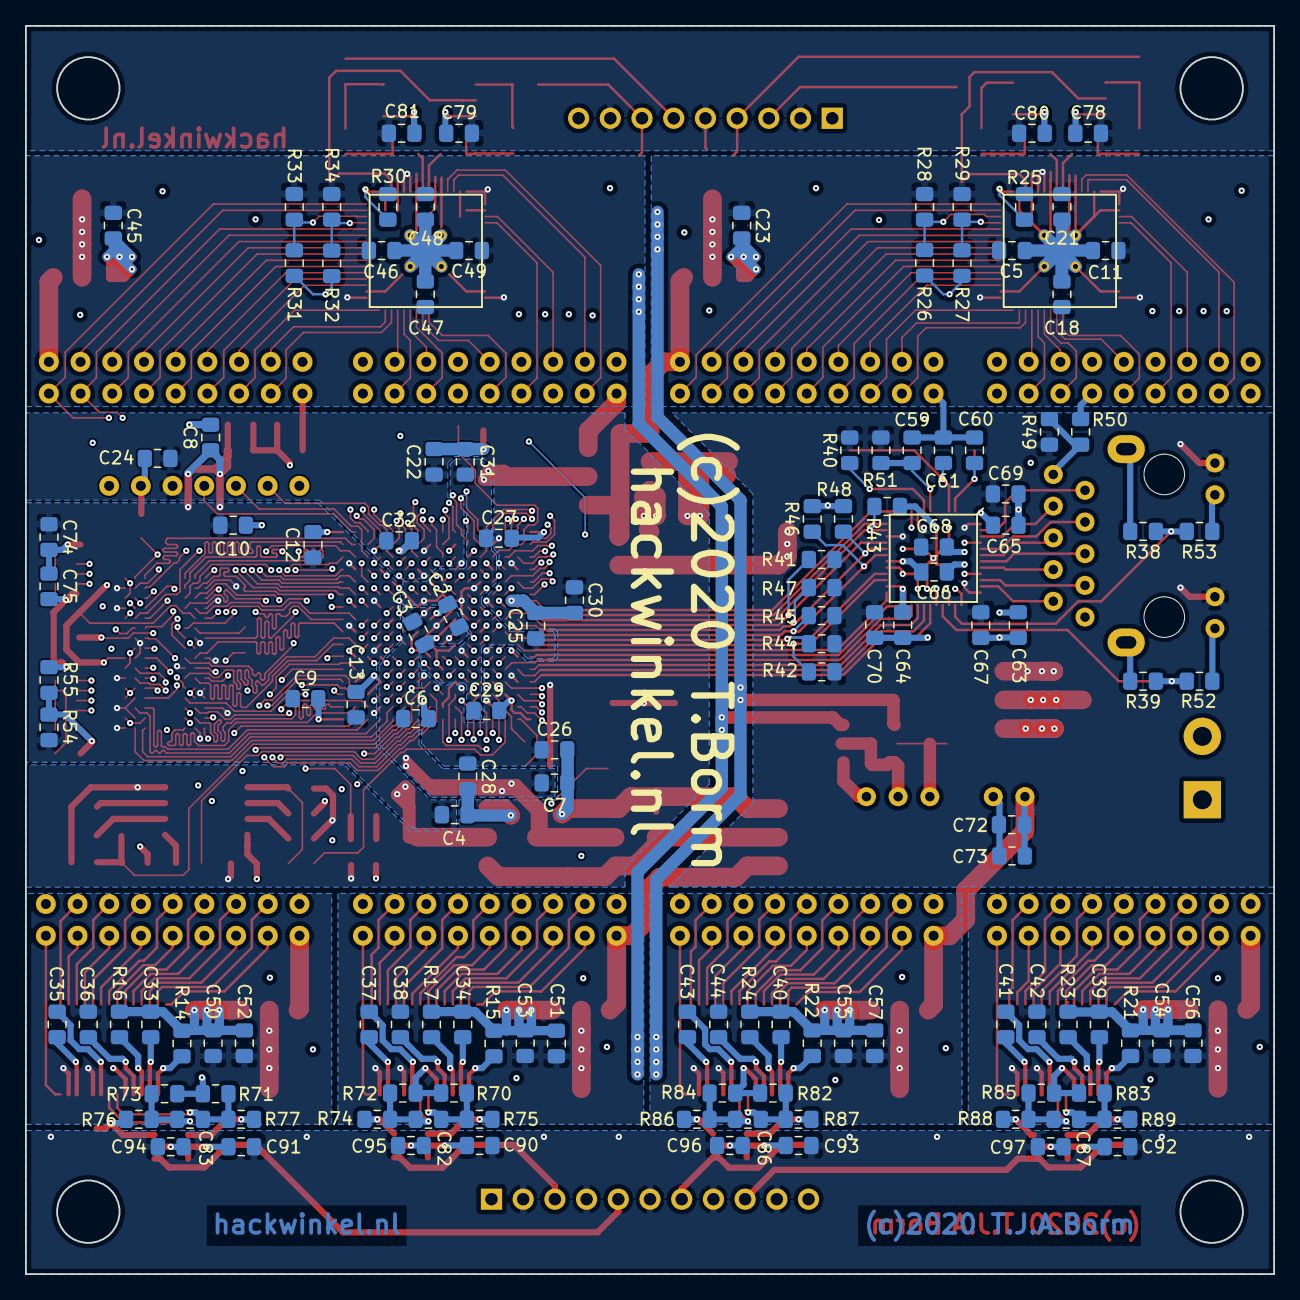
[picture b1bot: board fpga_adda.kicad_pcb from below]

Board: 4 copper layers, 100.0 x 100.0 mm, 242 parts (133 on the bottom side), 300 nets.

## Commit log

2021-05-05 initial dump
2021-05-05 format README
2021-05-05 typos
